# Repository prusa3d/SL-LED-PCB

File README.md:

# PRUSA SL-LED board

KiCad PCB layout

* [Interactive bom](http://htmlpreview.github.io/?https://github.com/prusa3d/SL-LED-PCB/blob/master/rev.02c/ibom.html)
* [STEP 3D model](rev.02c/LED-SLA-02c.step)

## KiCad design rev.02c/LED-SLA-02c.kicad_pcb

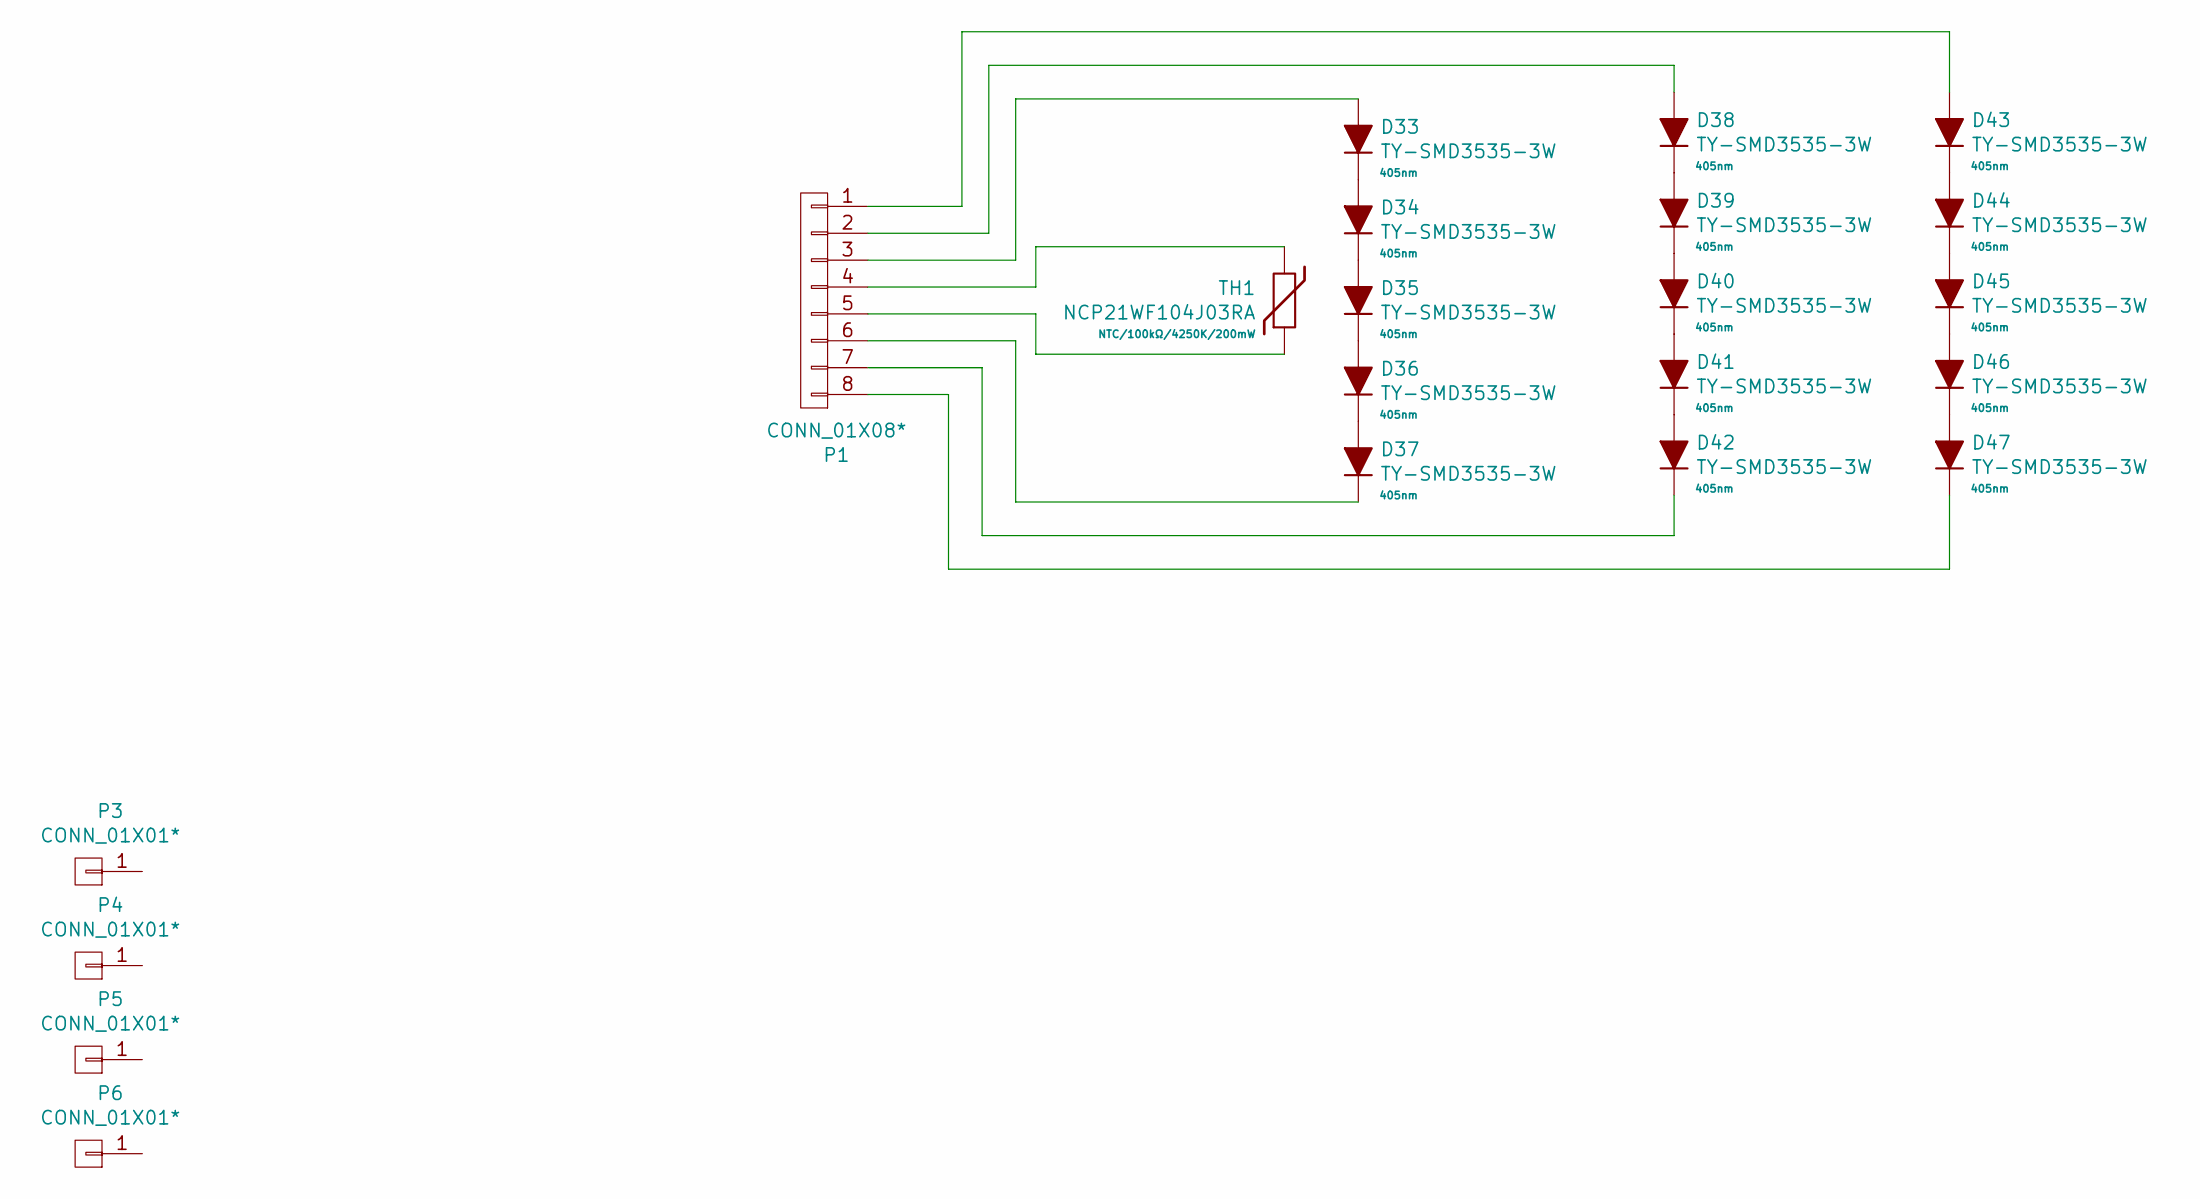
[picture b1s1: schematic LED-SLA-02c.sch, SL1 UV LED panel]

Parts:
D33, D34, D35, D36, D37, D38, D39, D40, D41, D42, D43, D44, D45, D46, D47: TY-SMD3535-3W; LED-UV-LTPL-C034UVH405
P1: CONN_01X08*; MX-172159-0608
P3, P4, P5, P6: CONN_01X01*; MountingHole_4.5mm
TH1: NCP21WF104J03RA; R_0805

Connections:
unnamed: D33.1 (K), D34.2 (A)
unnamed: D33.2 (A), P1.3
unnamed: D34.1 (K), D35.2 (A)
unnamed: D35.1 (K), D36.2 (A)
unnamed: D36.1 (K), D37.2 (A)
unnamed: D37.1 (K), P1.6
unnamed: D38.1 (K), D39.2 (A)
unnamed: D38.2 (A), P1.2
unnamed: D39.1 (K), D40.2 (A)
unnamed: D40.1 (K), D41.2 (A)
unnamed: D41.1 (K), D42.2 (A)
unnamed: D42.1 (K), P1.7
unnamed: D43.1 (K), D44.2 (A)
unnamed: D43.2 (A), P1.1
unnamed: D44.1 (K), D45.2 (A)
unnamed: D45.1 (K), D46.2 (A)
unnamed: D46.1 (K), D47.2 (A)
unnamed: D47.1 (K), P1.8
unnamed: P1.4, TH1.2
unnamed: P1.5, TH1.1

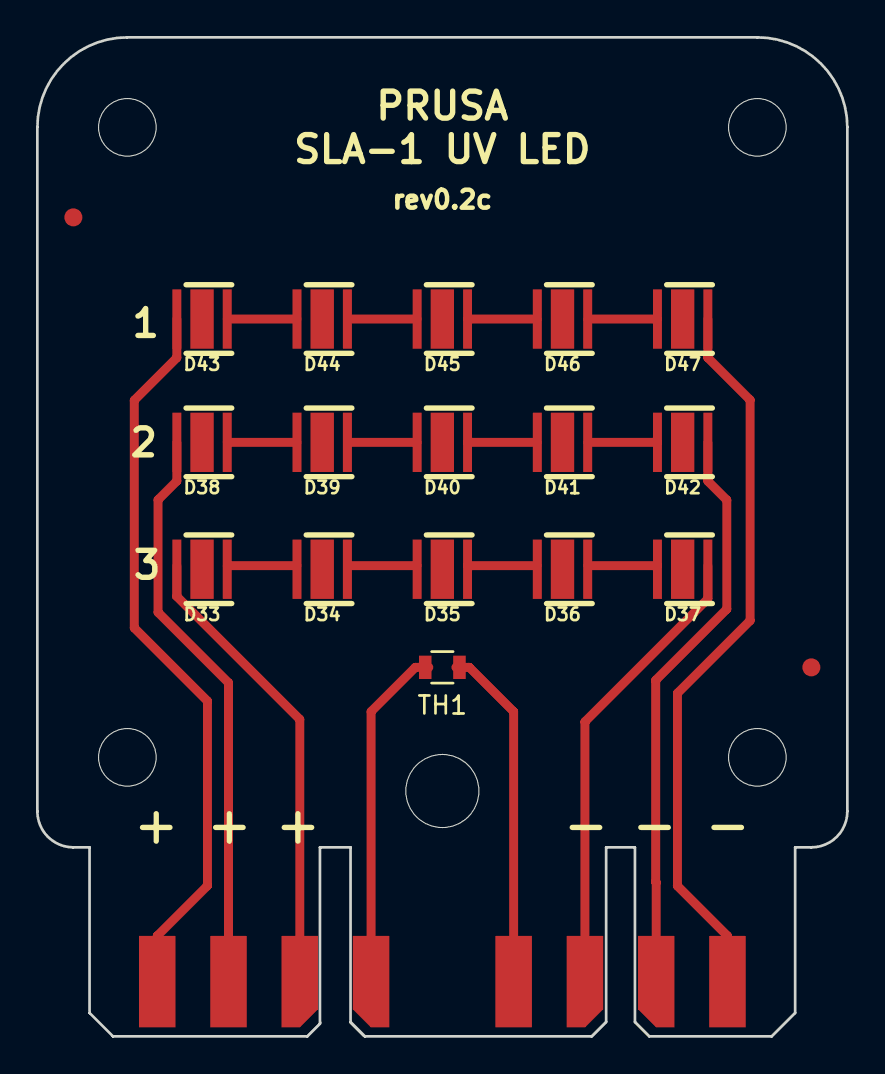
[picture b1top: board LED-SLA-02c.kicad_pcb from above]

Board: 2 copper layers, 45.0 x 55.5 mm, 21 parts (0 on the bottom side), 20 nets.

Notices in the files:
rev.02c/LED-SLA-02c.sch:
http://creativecommons.org/licenses/by-sa/4.0
Licensed under the Attribution-ShareAlike 4.0 International (CC BY-SA 4.0)
